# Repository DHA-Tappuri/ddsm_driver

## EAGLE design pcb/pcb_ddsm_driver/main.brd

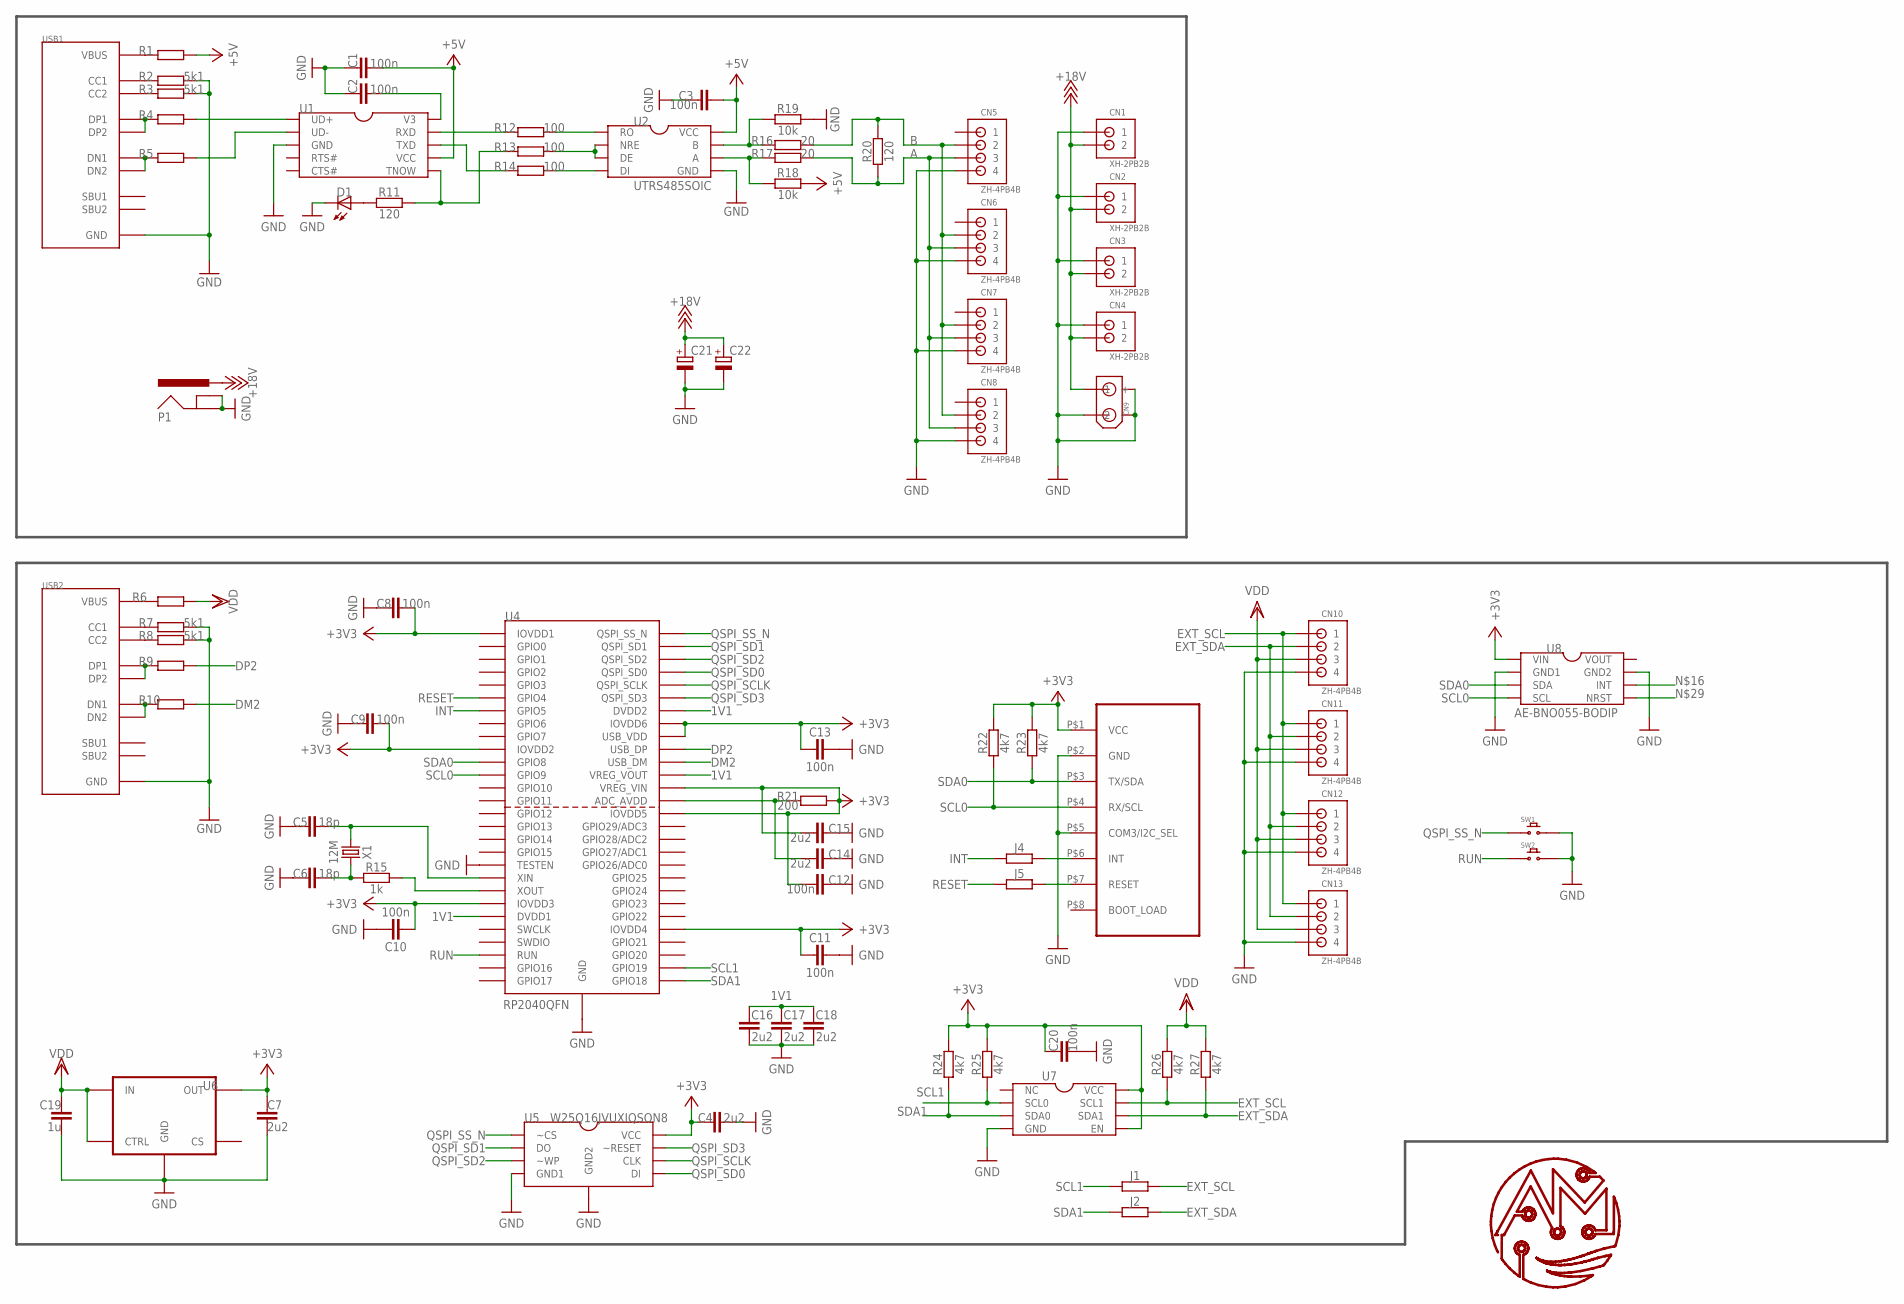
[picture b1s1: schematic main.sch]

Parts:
C1, C2, C3, C8, C9, C10, C11, C12, C13, C20: 100n; C1608
C4, C7, C14, C15, C16, C17, C18: 2u2; C1608
C5, C6: 18p; C1608
C19: 1u; C1608
C21, C22: E_CAPACITORRADIAL_D8; ECAP-D80-L115
CN1, CN2, CN3, CN4: XH-2PB2B; B2B-XH-A
CN5, CN6, CN7, CN8, CN10, CN11, CN12, CN13: ZH-4PB4B; B4B-ZR
CN9: XT60PW-MPCB; XT60PW-M
D1: LED1608R
J1, J2, J4, J5: JUMPER1608; J1608
P1: DC-JACKMJ179PH; MJ179PH
R1, R6: RESISTER3225; R3225
R2, R3, R7, R8: 5k1; R1608
R4, R5, R9, R10: RESISTER1608; R1608
R11, R20: 120; R1608
R12, R13, R14: 100; R1608
R15: 1k; R1608
R16, R17: 20; R1608
R18, R19: 10k; R1608
R21: 200; R1608
R22, R23, R24, R25, R26, R27: 4k7; R1608
SW1, SW2: TSY3420SMD-HOLE; TSY3420-HOLE
U1: CH340EMSOP; MSOP-05-10P
U2: UTRS485SOIC; SOIC-8P
U3: CJMCU-055SIP; CJMCU-055
U4: RP2040QFN; RP2040
U5: W25Q16JVUXIQSON8; W25Q16JVUXIQ
U6: REGULATOR2SOT23-5P; SOT23-5P
U7: PCA9515SOIC; PCA9515-SOIC
U8: AE-BNO055-BODIP; AE-BNO055-BO
U$2: LOGO8MM; LOGO-8MM
USB1, USB2: USB-CSMD; 5077CR-16-SMC2-BK-TR
X1: 12M; HC49S

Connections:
1V1: C16.P$1 (1), C17.P$1 (1), C18.P$1 (1), U4.P$23 (DVDD1), U4.P$45 (VREG_VOUT), U4.P$50 (DVDD2)
+3V3: C4.P$1 (1), C7.P$2 (2), C8.P$2 (2), C9.P$2 (2), C10.P$2 (2), C11.P$2 (2), C12.P$2 (2), C13.P$1 (1), C15.P$2 (2), C20.P$1 (1), R21.P$2 (2), R22.P$2 (2), R23.P$2 (2), R24.P$2 (2), R25.P$2 (2), U3.P$1 (VCC), U4.P$1 (IOVDD1), U4.P$10 (IOVDD2), U4.P$22 (IOVDD3), U4.P$33 (IOVDD4), U4.P$42 (IOVDD5), U4.P$44 (VREG_VIN), U4.P$48 (USB_VDD), U4.P$49 (IOVDD6), U5.P$8 (VCC), U6.P$5 (OUT), U7.P$5 (EN), U7.P$8 (VCC), U8.P$1 (VIN)
+5V: C1.P$2 (2), C3.P$1 (1), R1.P$2 (2), R18.P$1 (1), U1.P$7 (VCC), U2.P$8 (VCC)
+18V: C21.+, C22.+, CN1.2, CN2.2, CN3.2, CN4.2, CN9.P$1 (+), P1.VCC (PWR), P1.VCC1 (PWR)
A: CN5.3, CN6.3, CN7.3, CN8.3, R17.P$1 (1), R20.P$2 (2)
B: CN5.2, CN6.2, CN7.2, CN8.2, R16.P$1 (1), R20.P$1 (1)
DM2: R10.P$2 (2), U4.P$46 (USB_DM)
DP2: R9.P$2 (2), U4.P$47 (USB_DP)
EXT_SCL: CN10.1, CN11.1, CN12.1, CN13.1, J1.P$2 (2), R26.P$1 (1), U7.P$7 (SCL1)
EXT_SDA: CN10.2, CN11.2, CN12.2, CN13.2, J2.P$2 (2), R27.P$1 (1), U7.P$6 (SDA1)
GND: C1.P$1 (1), C2.P$1 (1), C3.P$2 (2), C4.P$2 (2), C5.P$1 (1), C6.P$1 (1), C7.P$1 (1), C8.P$1 (1), C9.P$1 (1), C10.P$1 (1), C11.P$1 (1), C12.P$1 (1), C13.P$2 (2), C14.P$1 (1), C15.P$1 (1), C16.P$2 (2), C17.P$2 (2), C18.P$2 (2), C19.P$1 (1), C20.P$2 (2), C21.-, C22.-, CN1.1, CN2.1, CN3.1, CN4.1, CN5.4, CN6.4, CN7.4, CN8.4, CN9.P$2 (-), CN9.P$3 (-1), CN9.P$4 (-2), CN9.P$5 (-1), CN9.P$6 (-2), CN10.4, CN11.4, CN12.4, CN13.4, D1.P$2 (K), P1.BREAK (GNDBREAK), P1.BREAK1 (GNDBREAK), P1.GND, P1.GND1 (GND), R2.P$2 (2), R3.P$2 (2), R7.P$2 (2), R8.P$2 (2), R19.P$1 (1), SW1.P$2, SW2.P$2, U1.P$3 (GND), U2.P$5 (GND), U3.P$2 (GND), U3.P$5 (COM3/I2C_SEL), U4.P$19 (TESTEN), U4.P$57 (GND), U5.P$4 (GND1), U5.P$9 (GND2), U6.P$2 (GND), U7.P$4 (GND), U8.P$2 (GND1), U8.P$7 (GND2), USB1.A1_B12 (GND), USB1.B1_A12 (GND), USB1.P$13 (GND), USB1.P$14 (GND), USB1.P$15 (GND), USB1.P$16 (GND), USB1.P$17 (GND), USB1.P$18 (GND), USB1.P$19 (GND), USB1.P$20 (GND), USB2.A1_B12 (GND), USB2.B1_A12 (GND), USB2.P$13 (GND), USB2.P$14 (GND), USB2.P$15 (GND), USB2.P$16 (GND), USB2.P$17 (GND), USB2.P$18 (GND), USB2.P$19 (GND), USB2.P$20 (GND)
INT: J4.P$1 (1), U4.P$7 (GPIO5)
unnamed: C6.P$2 (2), R15.P$1 (1), X1.1
unnamed: R4.P$1 (1), USB1.A6 (DP1), USB1.B6 (DP2)
unnamed: R5.P$1 (1), USB1.A7 (DN1), USB1.B7 (DN2)
unnamed: R9.P$1 (1), USB2.A6 (DP1), USB2.B6 (DP2)
unnamed: R10.P$1 (1), USB2.A7 (DN1), USB2.B7 (DN2)
unnamed: R1.P$1 (1), USB1.A4_B9 (VBUS), USB1.B4_A9 (VBUS)
unnamed: R7.P$1 (1), USB2.A5 (CC1)
unnamed: R2.P$1 (1), USB1.A5 (CC1)
unnamed: R8.P$1 (1), USB2.B5 (CC2)
unnamed: R3.P$1 (1), USB1.B5 (CC2)
unnamed: R6.P$1 (1), USB2.A4_B9 (VBUS), USB2.B4_A9 (VBUS)
unnamed: R11.P$1 (1), R13.P$2 (2), U1.P$6 (TNOW)
unnamed: D1.P$1 (A), R11.P$2 (2)
unnamed: R4.P$2 (2), U1.P$1 (UD+)
unnamed: J4.P$2 (2), U3.P$6 (INT), U8.P$6 (INT)
unnamed: R5.P$2 (2), U1.P$2 (UD-)
unnamed: R13.P$1 (1), U2.P$2 (NRE), U2.P$3 (DE)
unnamed: C2.P$2 (2), U1.P$10 (V3)
unnamed: R12.P$1 (1), U2.P$1 (RO)
unnamed: R14.P$1 (1), U2.P$4 (DI)
unnamed: R12.P$2 (2), U1.P$9 (RXD)
unnamed: R14.P$2 (2), U1.P$8 (TXD)
unnamed: C5.P$2 (2), U4.P$20 (XIN), X1.2
unnamed: R15.P$2 (2), U4.P$21 (XOUT)
unnamed: R16.P$2 (2), R19.P$2 (2), U2.P$7 (B)
unnamed: R17.P$2 (2), R18.P$2 (2), U2.P$6 (A)
unnamed: C14.P$2 (2), R21.P$1 (1), U4.P$43 (ADC_AVDD)
unnamed: J5.P$2 (2), U3.P$7 (RESET), U8.P$5 (NRST)
QSPI_SCLK: U4.P$52 (QSPI_SCLK), U5.P$6 (CLK)
QSPI_SD0: U4.P$53 (QSPI_SD0), U5.P$5 (DI)
QSPI_SD1: U4.P$55 (QSPI_SD1), U5.P$2 (DO)
QSPI_SD2: U4.P$54 (QSPI_SD2), U5.P$3 (~WP)
QSPI_SD3: U4.P$51 (QSPI_SD3), U5.P$7 (~RESET)
QSPI_SS_N: SW1.P$1, U4.P$56 (QSPI_SS_N), U5.P$1 (~CS)
RESET: J5.P$1 (1), U4.P$6 (GPIO4)
RUN: SW2.P$1, U4.P$26 (RUN)
SCL0: R22.P$1 (1), U3.P$4 (RX/SCL), U4.P$12 (GPIO9), U8.P$4 (SCL)
SCL1: J1.P$1 (1), R25.P$1 (1), U4.P$30 (GPIO19), U7.P$2 (SCL0)
SDA0: R23.P$1 (1), U3.P$3 (TX/SDA), U4.P$11 (GPIO8), U8.P$3 (SDA)
SDA1: J2.P$1 (1), R24.P$1 (1), U4.P$29 (GPIO18), U7.P$3 (SDA0)
VDD: C19.P$2 (2), CN10.3, CN11.3, CN12.3, CN13.3, R6.P$2 (2), R26.P$2 (2), R27.P$2 (2), U6.P$1 (IN), U6.P$3 (CTRL)

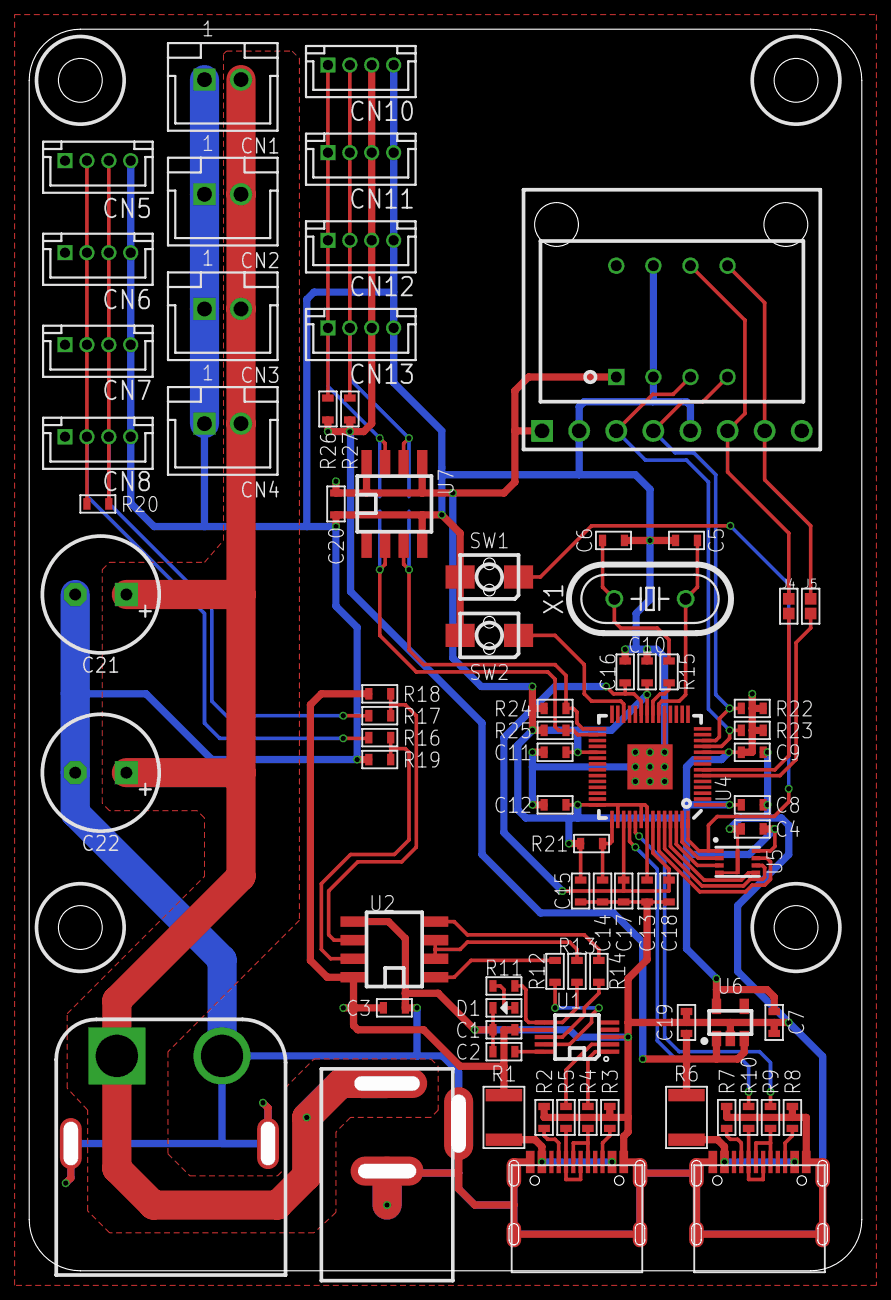
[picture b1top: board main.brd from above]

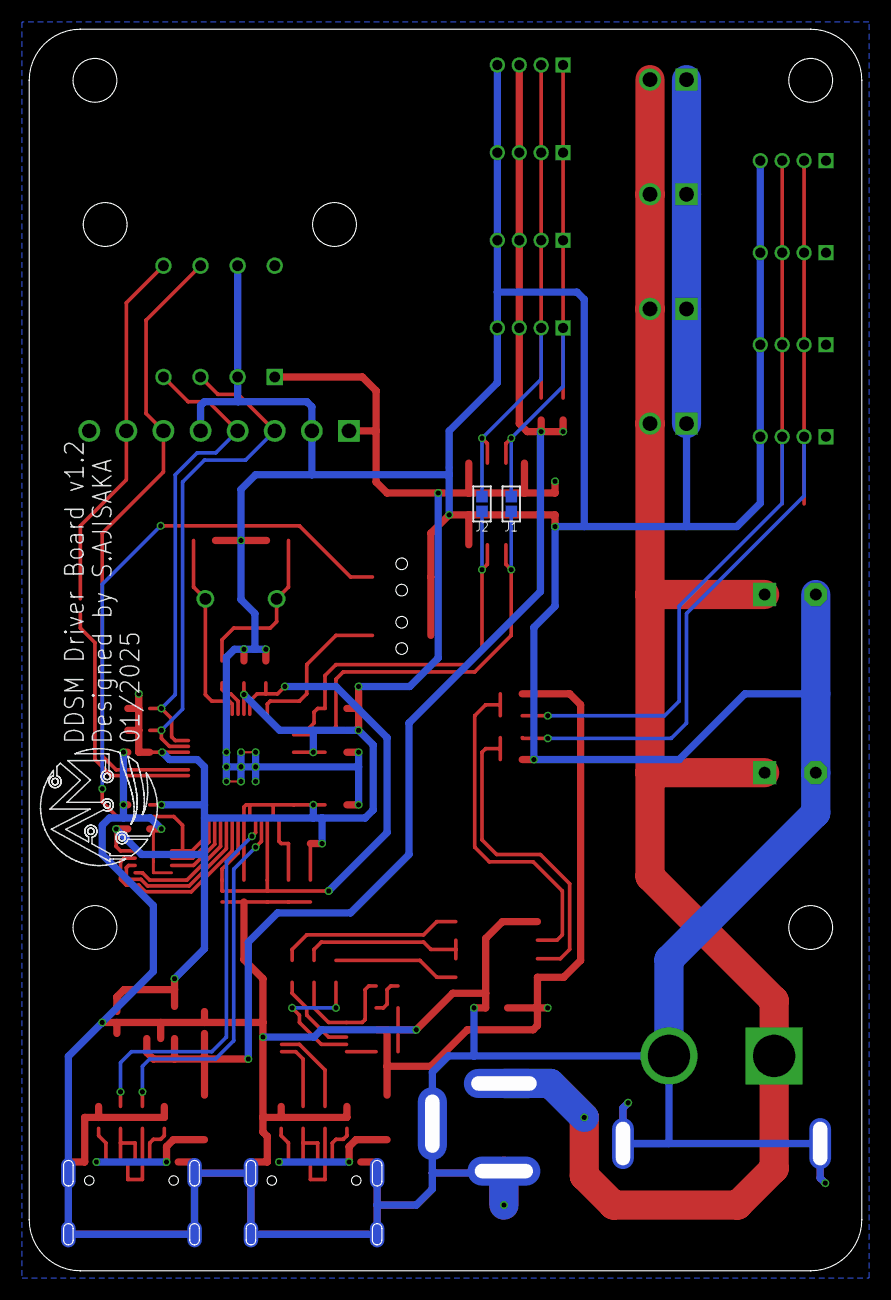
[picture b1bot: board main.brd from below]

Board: 2 copper layers, 57.0 x 85.0 mm, 82 parts (3 on the bottom side), 53 nets.

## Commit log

2025-02-17 working commit
2025-02-17 add yaml setting file
2025-02-17 add ID change node
2025-02-20 add launch file and config file
